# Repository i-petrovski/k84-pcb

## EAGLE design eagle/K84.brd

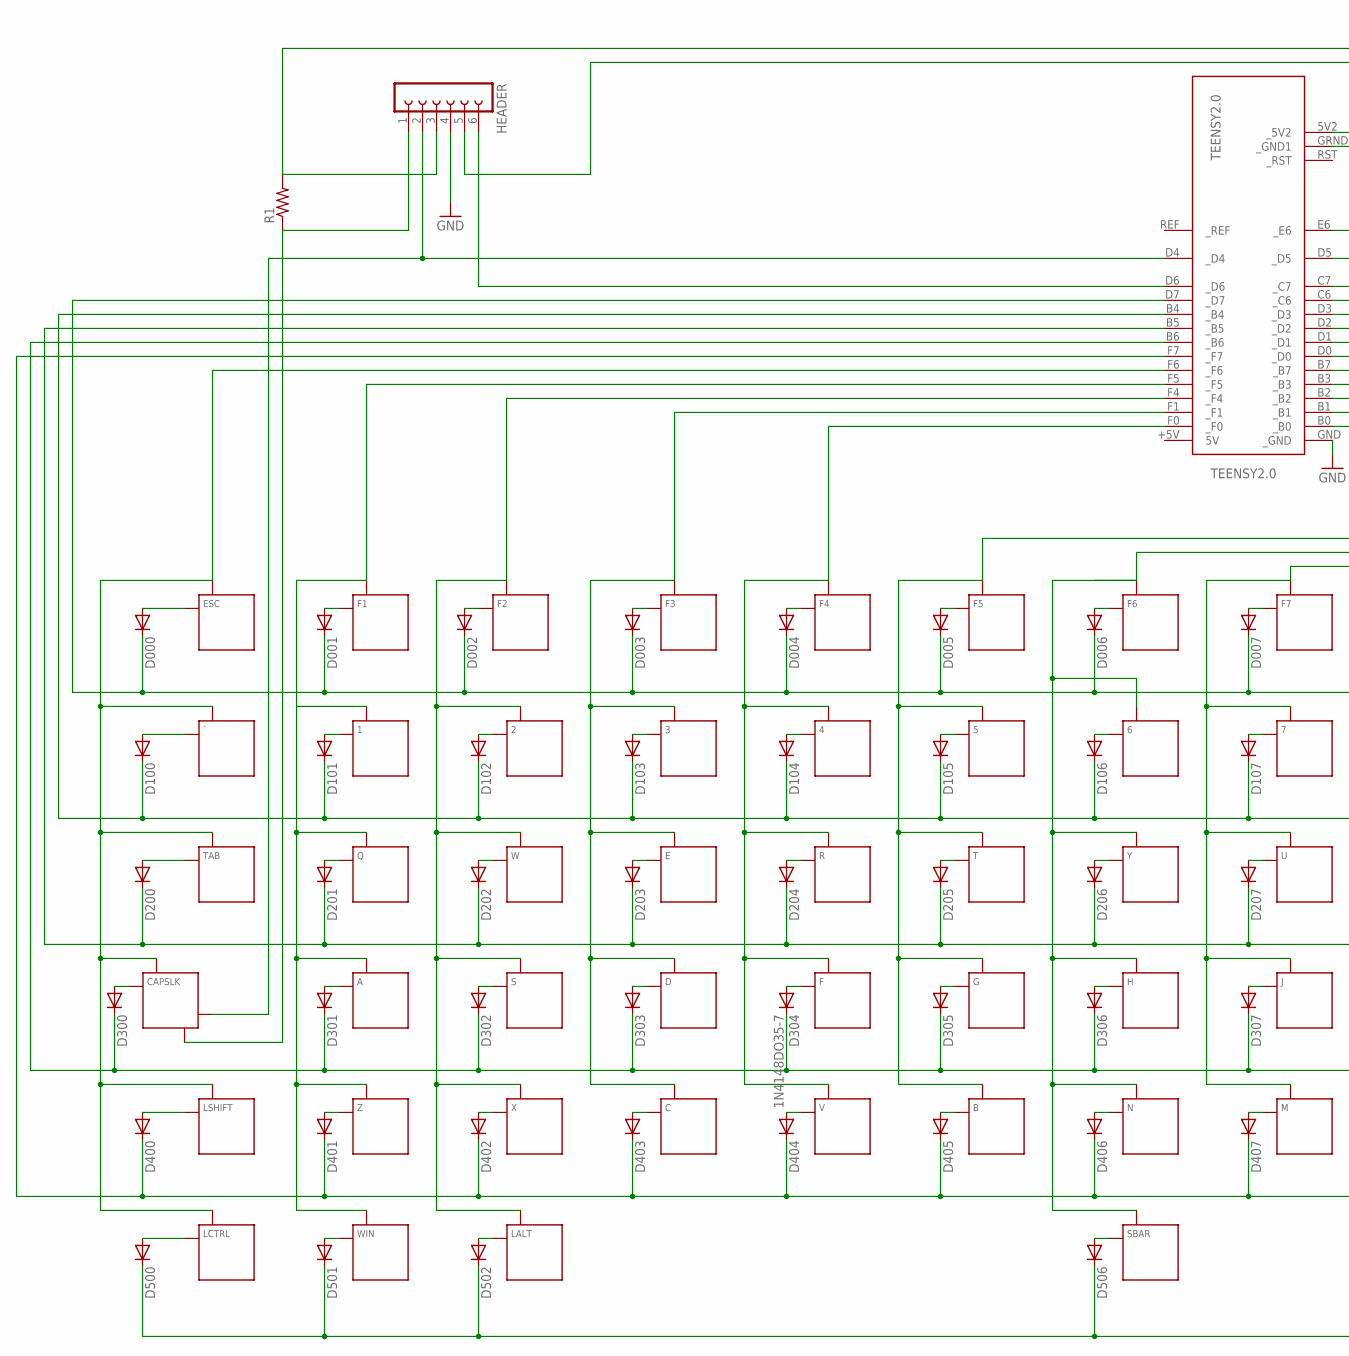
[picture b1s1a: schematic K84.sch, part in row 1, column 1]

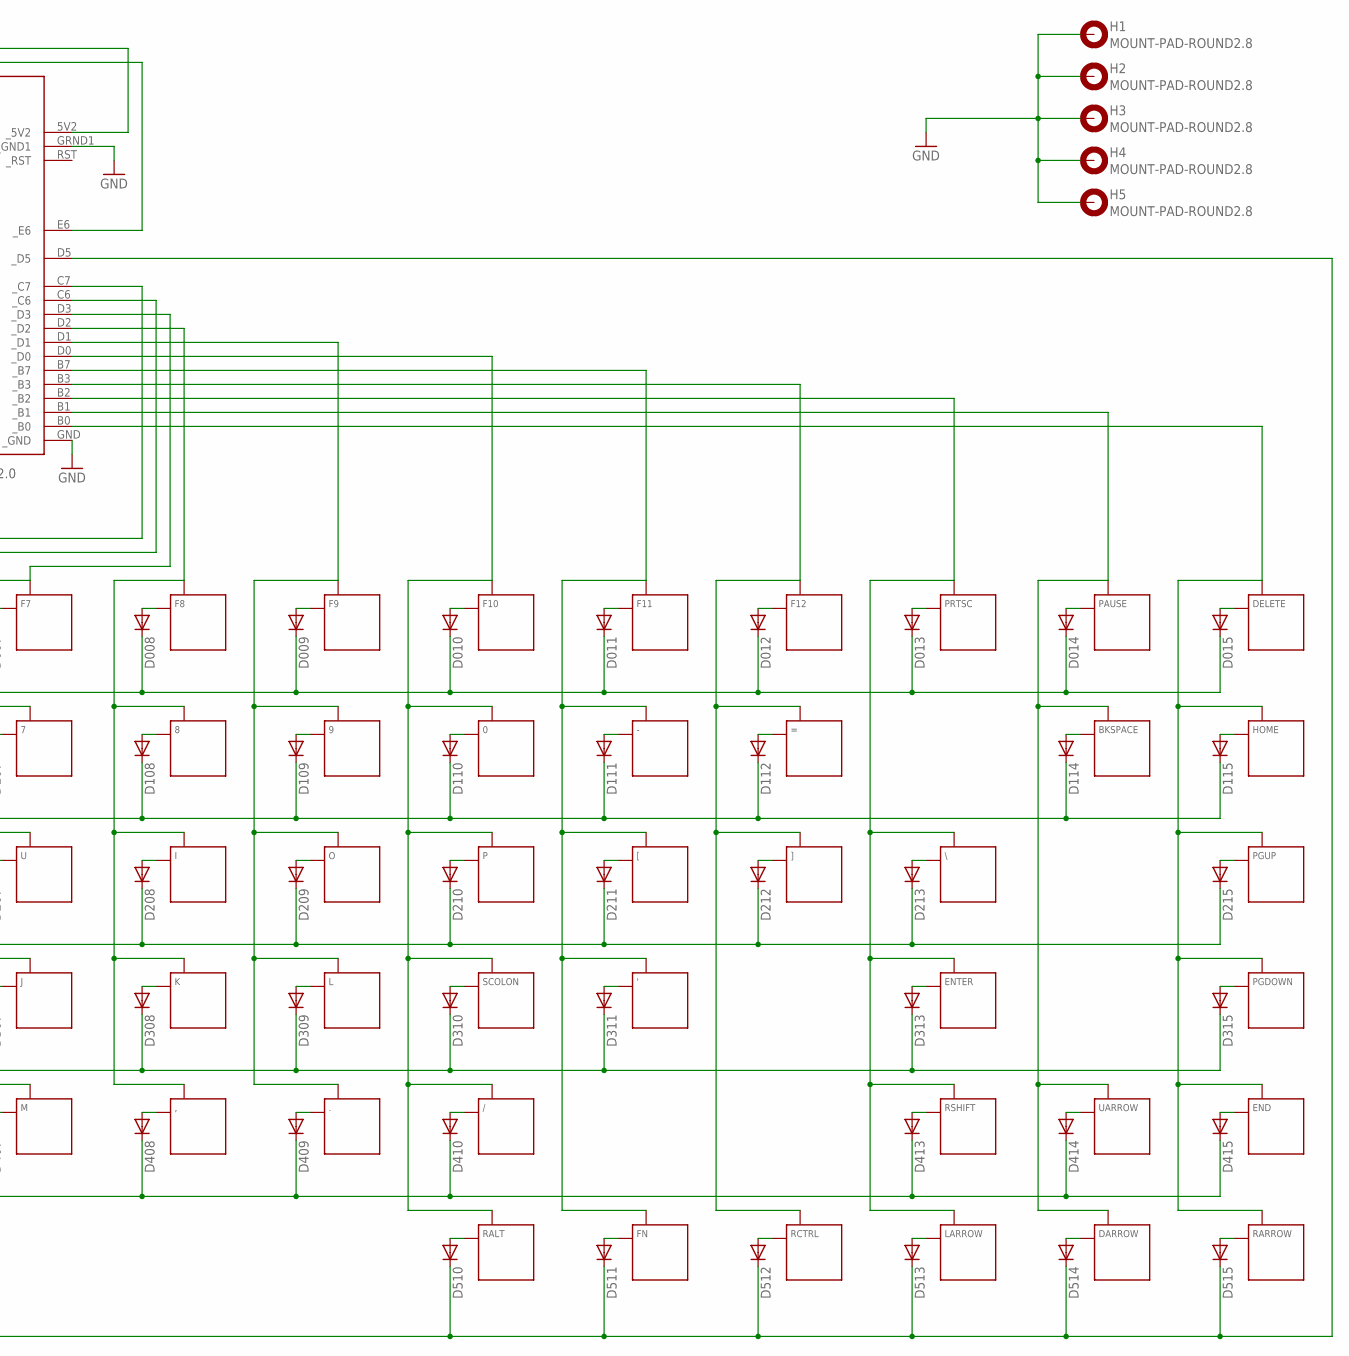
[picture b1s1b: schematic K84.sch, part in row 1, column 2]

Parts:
0, 1, 2, 3, 4, 5, 6, 7, 8, 9, .: KEYSWITCH-PLAIN-MX-1U; MX-1U
': KEYSWITCH-PLAIN-MX-1U; MX-1U
,: KEYSWITCH-PLAIN-MX-1U; MX-1U
-: KEYSWITCH-PLAIN-MX-1U; MX-1U
/: KEYSWITCH-PLAIN-MX-1U; MX-1U
=: KEYSWITCH-PLAIN-MX-1U; MX-1U
A: KEYSWITCH-PLAIN-MX-1U; MX-1U
B: KEYSWITCH-PLAIN-MX-1U; MX-1U
BKSPACE: KEYSWITCH-PLAIN-MX-2U; MX-2U
C: KEYSWITCH-PLAIN-MX-1U; MX-1U
CAPSLK: KEYSWITCH-LED-MX-1U-LED; MX-1U-LED
D: KEYSWITCH-PLAIN-MX-1U; MX-1U
D000, D001, D002, D003, D004, D005, D006, D007, D008, D009, D010, D011, D012, D013, D014, D015, D100, D101, D102, D103, D104, D105, D106, D107, D108, D109, D110, D111, D112, D114, D115, D200, D201, D202, D203, D204, D205, D206, D207, D208, D209, D210, D211, D212, D213, D215, D300, D301, D302, D303, D304, D305, D306, D307, D308, D309, D310, D311, D313, D315, D400, D401, D402, D403, D404, D405, D406, D407, D408, D409, D410, D413, D414, D415, D500, D501, D502, D506, D510, D511, D512, D513, D514, D515: 1N4148DO35-7; DO35-7
DARROW: KEYSWITCH-PLAIN-MX-1U; MX-1U
DELETE: KEYSWITCH-PLAIN-MX-1U; MX-1U
E: KEYSWITCH-PLAIN-MX-1U; MX-1U
END: KEYSWITCH-PLAIN-MX-1U; MX-1U
ENTER: KEYSWITCH-PLAIN-MX-2U; MX-2U
ESC: S001; MX-1U
F, F1, F2, F3, F4, F5, F6, F7, F8, F9, F10, F11, F12: KEYSWITCH-PLAIN-MX-1U; MX-1U
FN: KEYSWITCH-PLAIN-MX-1U; MX-1U
G: KEYSWITCH-PLAIN-MX-1U; MX-1U
H: KEYSWITCH-PLAIN-MX-1U; MX-1U
H1, H2, H3, H4, H5: MOUNT-PAD-ROUND2.8; 2,8-PAD
HEADER: FE06-1; FE06
HOME: KEYSWITCH-PLAIN-MX-1U; MX-1U
I: KEYSWITCH-PLAIN-MX-1U; MX-1U
J: KEYSWITCH-PLAIN-MX-1U; MX-1U
K: KEYSWITCH-PLAIN-MX-1U; MX-1U
L: KEYSWITCH-PLAIN-MX-1U; MX-1U
LALT: KEYSWITCH-PLAIN-MX-1U; MX-1U
LARROW: KEYSWITCH-PLAIN-MX-1U; MX-1U
LCTRL: KEYSWITCH-PLAIN-MX-1U; MX-1U
LSHIFT: KEYSWITCH-PLAIN-MX-2U; MX-2U
M: KEYSWITCH-PLAIN-MX-1U; MX-1U
N: KEYSWITCH-PLAIN-MX-1U; MX-1U
O: KEYSWITCH-PLAIN-MX-1U; MX-1U
P: KEYSWITCH-PLAIN-MX-1U; MX-1U
PAUSE: KEYSWITCH-PLAIN-MX-1U; MX-1U
PGDOWN: KEYSWITCH-PLAIN-MX-1U; MX-1U
PGUP: KEYSWITCH-PLAIN-MX-1U; MX-1U
PRTSC: KEYSWITCH-PLAIN-MX-1U; MX-1U
Q: KEYSWITCH-PLAIN-MX-1U; MX-1U
R: KEYSWITCH-PLAIN-MX-1U; MX-1U
R1: R-US_0204/7; 0204/7
RALT: KEYSWITCH-PLAIN-MX-1U; MX-1U
RARROW: KEYSWITCH-PLAIN-MX-1U; MX-1U
RCTRL: KEYSWITCH-PLAIN-MX-1U; MX-1U
RSHIFT: KEYSWITCH-PLAIN-MX-1U; MX-1U
S: KEYSWITCH-PLAIN-MX-1U; MX-1U
SBAR: KEYSWITCH-PLAIN-MX-6.25U-FLIPPED; MX-6.25U-FLIPPED
SCOLON: KEYSWITCH-PLAIN-MX-1U; MX-1U
T: KEYSWITCH-PLAIN-MX-1U; MX-1U
TAB: KEYSWITCH-PLAIN-MX-1U; MX-1U
TEENSY2.0: TEENSY2.0
U: KEYSWITCH-PLAIN-MX-1U; MX-1U
UARROW: KEYSWITCH-PLAIN-MX-1U; MX-1U
V: KEYSWITCH-PLAIN-MX-1U; MX-1U
W: KEYSWITCH-PLAIN-MX-1U; MX-1U
WIN: KEYSWITCH-PLAIN-MX-1U; MX-1U
X: KEYSWITCH-PLAIN-MX-1U; MX-1U
Y: KEYSWITCH-PLAIN-MX-1U; MX-1U
Z: KEYSWITCH-PLAIN-MX-1U; MX-1U
[: KEYSWITCH-PLAIN-MX-1U; MX-1U
\\: KEYSWITCH-PLAIN-MX-1U; MX-1U
]: KEYSWITCH-PLAIN-MX-1U; MX-1U
`: KEYSWITCH-PLAIN-MX-1U; MX-1U

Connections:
5V2: HEADER.3, R1.2, TEENSY2.0.5V2 (_5V2)
B0: DELETE.MX2 (P1), END.MX2 (P1), HOME.MX2 (P1), PGDOWN.MX2 (P1), PGUP.MX2 (P1), RARROW.MX2 (P1), TEENSY2.0.B0 (_B0)
B1: BKSPACE.MX2 (P1), DARROW.MX2 (P1), PAUSE.MX2 (P1), TEENSY2.0.B1 (_B1), UARROW.MX2 (P1)
B2: ENTER.MX2 (P1), LARROW.MX2 (P1), PRTSC.MX2 (P1), RSHIFT.MX2 (P1), TEENSY2.0.B2 (_B2), \\.MX2 (P1)
B3: =.MX2 (P1), F12.MX2 (P1), RCTRL.MX2 (P1), TEENSY2.0.B3 (_B3), ].MX2 (P1)
B4: D100.C, D101.C, D102.C, D103.C, D104.C, D105.C, D106.C, D107.C, D108.C, D109.C, D110.C, D111.C, D112.C, D114.C, D115.C, TEENSY2.0.B4 (_B4)
B5: D200.C, D201.C, D202.C, D203.C, D204.C, D205.C, D206.C, D207.C, D208.C, D209.C, D210.C, D211.C, D212.C, D213.C, D215.C, TEENSY2.0.B5 (_B5)
B6: D300.C, D301.C, D302.C, D303.C, D304.C, D305.C, D306.C, D307.C, D308.C, D309.C, D310.C, D311.C, D313.C, D315.C, TEENSY2.0.B6 (_B6)
B7: '.MX2 (P1), -.MX2 (P1), F11.MX2 (P1), FN.MX2 (P1), TEENSY2.0.B7 (_B7), [.MX2 (P1)
C6: 6.MX2 (P1), F6.MX2 (P1), H.MX2 (P1), N.MX2 (P1), SBAR.MX2 (P1), TEENSY2.0.C6 (_C6), Y.MX2 (P1)
C7: 5.MX2 (P1), B.MX2 (P1), F5.MX2 (P1), G.MX2 (P1), T.MX2 (P1), TEENSY2.0.C7 (_C7)
CAPS-LED+: CAPSLK.LED+, HEADER.1, R1.1
D0: 0.MX2 (P1), /.MX2 (P1), F10.MX2 (P1), P.MX2 (P1), RALT.MX2 (P1), SCOLON.MX2 (P1), TEENSY2.0.D0 (_D0)
D1: 9.MX2 (P1), ..MX2 (P1), F9.MX2 (P1), L.MX2 (P1), O.MX2 (P1), TEENSY2.0.D1 (_D1)
D2: 8.MX2 (P1), ,.MX2 (P1), F8.MX2 (P1), I.MX2 (P1), K.MX2 (P1), TEENSY2.0.D2 (_D2)
D3: 7.MX2 (P1), F7.MX2 (P1), J.MX2 (P1), M.MX2 (P1), TEENSY2.0.D3 (_D3), U.MX2 (P1)
D4: CAPSLK.LED-, HEADER.2, TEENSY2.0.D4 (_D4)
D5: D500.C, D501.C, D502.C, D506.C, D510.C, D511.C, D512.C, D513.C, D514.C, D515.C, TEENSY2.0.D5 (_D5)
D7: D000.C, D001.C, D002.C, D003.C, D004.C, D005.C, D006.C, D007.C, D008.C, D009.C, D010.C, D011.C, D012.C, D013.C, D014.C, D015.C, TEENSY2.0.D7 (_D7)
F0: 4.MX2 (P1), F.MX2 (P1), F4.MX2 (P1), R.MX2 (P1), TEENSY2.0.F0 (_F0), V.MX2 (P1)
F1: 3.MX2 (P1), C.MX2 (P1), D.MX2 (P1), E.MX2 (P1), F3.MX2 (P1), TEENSY2.0.F1 (_F1)
F4: 2.MX2 (P1), F2.MX2 (P1), LALT.MX2 (P1), S.MX2 (P1), TEENSY2.0.F4 (_F4), W.MX2 (P1), X.MX2 (P1)
F5: 1.MX2 (P1), A.MX2 (P1), F1.MX2 (P1), Q.MX2 (P1), TEENSY2.0.F5 (_F5), WIN.MX2 (P1), Z.MX2 (P1)
F6: CAPSLK.MX2 (P1), ESC.MX2 (P1), LCTRL.MX2 (P1), LSHIFT.MX2 (P1), TAB.MX2 (P1), TEENSY2.0.F6 (_F6), `.MX2 (P1)
F7: D400.C, D401.C, D402.C, D403.C, D404.C, D405.C, D406.C, D407.C, D408.C, D409.C, D410.C, D413.C, D414.C, D415.C, TEENSY2.0.F7 (_F7)
GND: H1.B2,8, H2.B2,8, H3.B2,8, H4.B2,8, H5.B2,8, HEADER.4, TEENSY2.0.GND (_GND), TEENSY2.0.GRND1 (_GND1)
unnamed: D000.A, ESC.MX1 (P0)
unnamed: D001.A, F1.MX1 (P0)
unnamed: D002.A, F2.MX1 (P0)
unnamed: D115.A, HOME.MX1 (P0)
unnamed: D003.A, F3.MX1 (P0)
unnamed: D004.A, F4.MX1 (P0)
unnamed: D100.A, `.MX1 (P0)
unnamed: D011.A, F11.MX1 (P0)
unnamed: D005.A, F5.MX1 (P0)
unnamed: D006.A, F6.MX1 (P0)
unnamed: D007.A, F7.MX1 (P0)
unnamed: D008.A, F8.MX1 (P0)
unnamed: D009.A, F9.MX1 (P0)
unnamed: D013.A, PRTSC.MX1 (P0)
unnamed: D010.A, F10.MX1 (P0)
unnamed: 1.MX1 (P0), D101.A
unnamed: D012.A, F12.MX1 (P0)
unnamed: D014.A, PAUSE.MX1 (P0)
unnamed: 2.MX1 (P0), D102.A
unnamed: D015.A, DELETE.MX1 (P0)
unnamed: 3.MX1 (P0), D103.A
unnamed: 7.MX1 (P0), D107.A
unnamed: 4.MX1 (P0), D104.A
unnamed: 5.MX1 (P0), D105.A
unnamed: 6.MX1 (P0), D106.A
unnamed: 8.MX1 (P0), D108.A
unnamed: 9.MX1 (P0), D109.A
unnamed: 0.MX1 (P0), D110.A
unnamed: -.MX1 (P0), D111.A
unnamed: =.MX1 (P0), D112.A
unnamed: BKSPACE.MX1 (P0), D114.A
unnamed: D201.A, Q.MX1 (P0)
unnamed: D200.A, TAB.MX1 (P0)
unnamed: D308.A, K.MX1 (P0)
unnamed: D202.A, W.MX1 (P0)
unnamed: D302.A, S.MX1 (P0)
unnamed: A.MX1 (P0), D301.A
unnamed: D402.A, X.MX1 (P0)
unnamed: D401.A, Z.MX1 (P0)
unnamed: C.MX1 (P0), D403.A
unnamed: D304.A, F.MX1 (P0)
unnamed: D204.A, R.MX1 (P0)
unnamed: D404.A, V.MX1 (P0)
unnamed: B.MX1 (P0), D405.A
unnamed: D305.A, G.MX1 (P0)
unnamed: D.MX1 (P0), D303.A
unnamed: D205.A, T.MX1 (P0)
unnamed: D206.A, Y.MX1 (P0)
unnamed: D207.A, U.MX1 (P0)
unnamed: D307.A, J.MX1 (P0)
unnamed: D407.A, M.MX1 (P0)
unnamed: D406.A, N.MX1 (P0)
unnamed: D306.A, H.MX1 (P0)
unnamed: D208.A, I.MX1 (P0)
unnamed: D209.A, O.MX1 (P0)
unnamed: D309.A, L.MX1 (P0)
unnamed: ..MX1 (P0), D409.A
unnamed: ,.MX1 (P0), D408.A
unnamed: /.MX1 (P0), D410.A
unnamed: D310.A, SCOLON.MX1 (P0)
unnamed: D210.A, P.MX1 (P0)
unnamed: D211.A, [.MX1 (P0)
unnamed: '.MX1 (P0), D311.A
unnamed: D400.A, LSHIFT.MX1 (P0)
unnamed: D212.A, ].MX1 (P0)
unnamed: D213.A, \\.MX1 (P0)
unnamed: D313.A, ENTER.MX1 (P0)
unnamed: D215.A, PGUP.MX1 (P0)
unnamed: D315.A, PGDOWN.MX1 (P0)
unnamed: D415.A, END.MX1 (P0)
unnamed: D414.A, UARROW.MX1 (P0)
unnamed: D515.A, RARROW.MX1 (P0)
unnamed: D514.A, DARROW.MX1 (P0)
unnamed: D513.A, LARROW.MX1 (P0)
unnamed: D413.A, RSHIFT.MX1 (P0)
unnamed: D512.A, RCTRL.MX1 (P0)
unnamed: D511.A, FN.MX1 (P0)
unnamed: D510.A, RALT.MX1 (P0)
unnamed: CAPSLK.MX1 (P0), D300.A
unnamed: D203.A, E.MX1 (P0)
unnamed: HEADER.6, TEENSY2.0.D6 (_D6)
unnamed: HEADER.5, TEENSY2.0.E6 (_E6)
unnamed: D500.A, LCTRL.MX1 (P0)
unnamed: D501.A, WIN.MX1 (P0)
unnamed: D502.A, LALT.MX1 (P0)
unnamed: D506.A, SBAR.MX1 (P0)

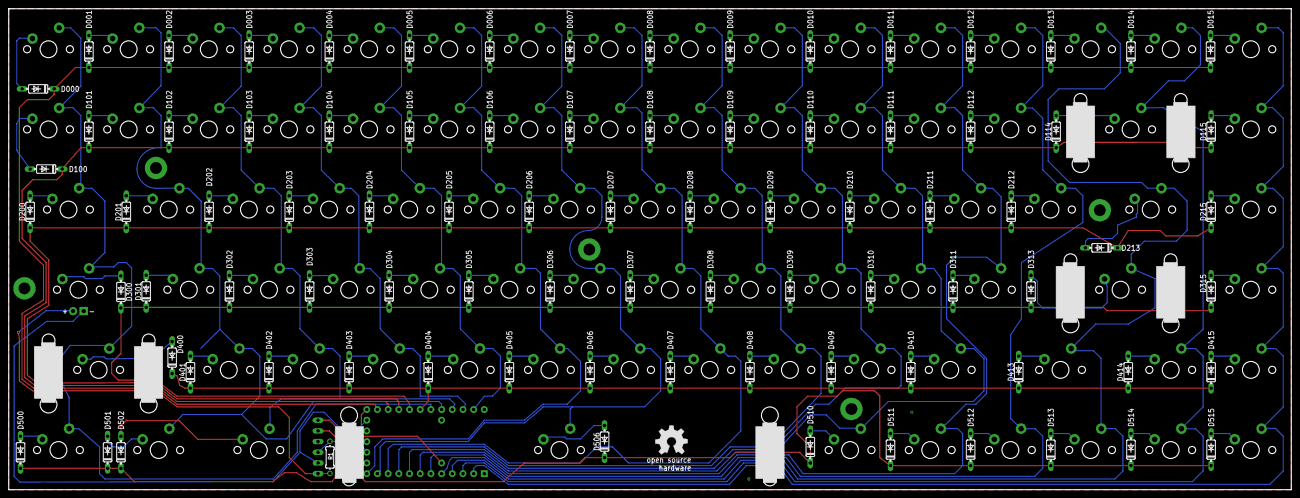
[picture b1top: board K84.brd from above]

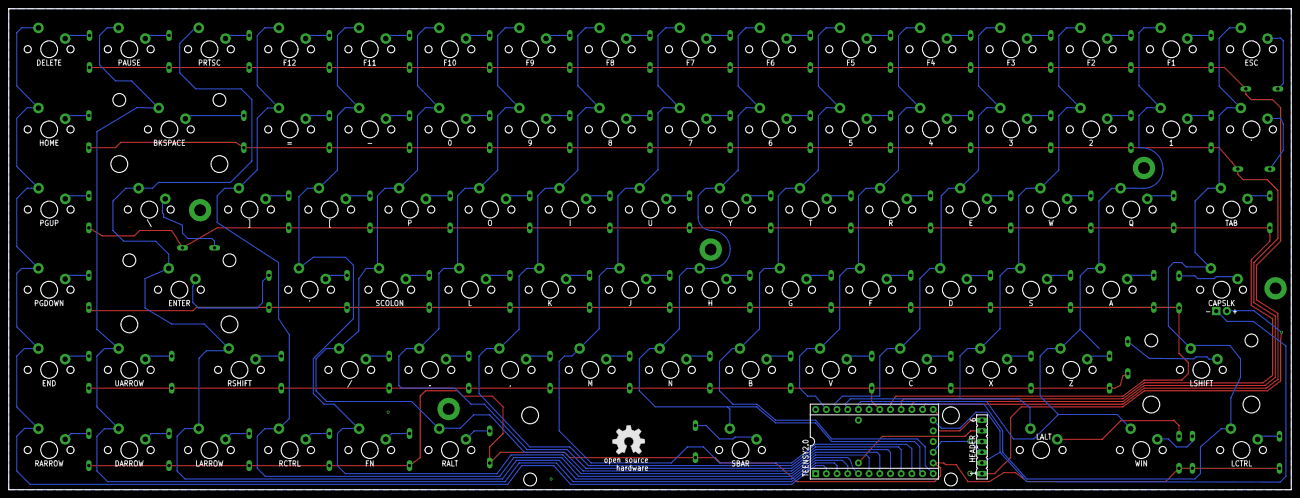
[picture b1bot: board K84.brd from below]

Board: 2 copper layers, 304.8 x 114.3 mm, 178 parts (3 on the bottom side), 112 nets.

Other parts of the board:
U$1, U$2: OSHW_8MM

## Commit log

2019-05-31 adding PCB eagle files
